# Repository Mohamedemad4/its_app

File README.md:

# its_app

### Schematics and PCB notes
 - 
### Notes on the SIM868 Module
 - it *needs* it's 2A peak current recommend connecting power to a battery
 - APN doens't really matter what you call it (at least Etisalat egypt)

### Notes about data_server
 - there is a 30char **hard** limit on token names
 - Expected Hz is .5Hz 
    - i.e 30 logs is a minute of data
 - #### About tokens 
    - We have 2 kinds of tokens
        - Client Tokens
            - Set by "login" on the client 
            - Used for Push notifications and everything else client related by car_token agnostic

        - Car Tokens
            - Preset in QR code on the Device it self
            - Multiple Client tokens can be registered to the Same Car Token
    - *ALL* Tokens are expected to look like 
        ```xxxx-xxx-xxxx``
        this is very critical for Car Tokens since the client expects this to be the case before sending them to the Server 
### Config Vars

#### data_server/tests/test_api.py
- email is the email to register the token with
- ```CAR_DATA_KEYS``` is the JSON keys expected as the output of the API for for the getData
- ```TOKEN_METADATA_KEYS``` is the JSON keys expected outputs of the API for get_metadata
- ```NOTF_KEYS``` is the JSON keys expected output of the API for get_notfs
- ```real_hz``` how often (in hertz) do we send the data to the server?
- ```min_of_speeding_to_alert``` how many minutes should pass before warning the user to a speed_exceeding event?
    - see #17
```
    server_uri="http://localhost:7060"
    email="mohamed.emad4bubble@gmail.com"
    CAR_DATA_KEYS=["car_token","lat","lot","speed","accuracy","Unixtimestamp"]
    TOKEN_METADATA_KEYS=["car_token","client_token","max_spd"]
    NOTF_KEYS=["client_token","title","msg"]
    real_hz=.5
```
#### data_server/notf_man.py
How many logs should pass before sending a warning notf?
```
    self.MAX_THROT_ENTRIES=15 # 30 logs means a min of speeding
```

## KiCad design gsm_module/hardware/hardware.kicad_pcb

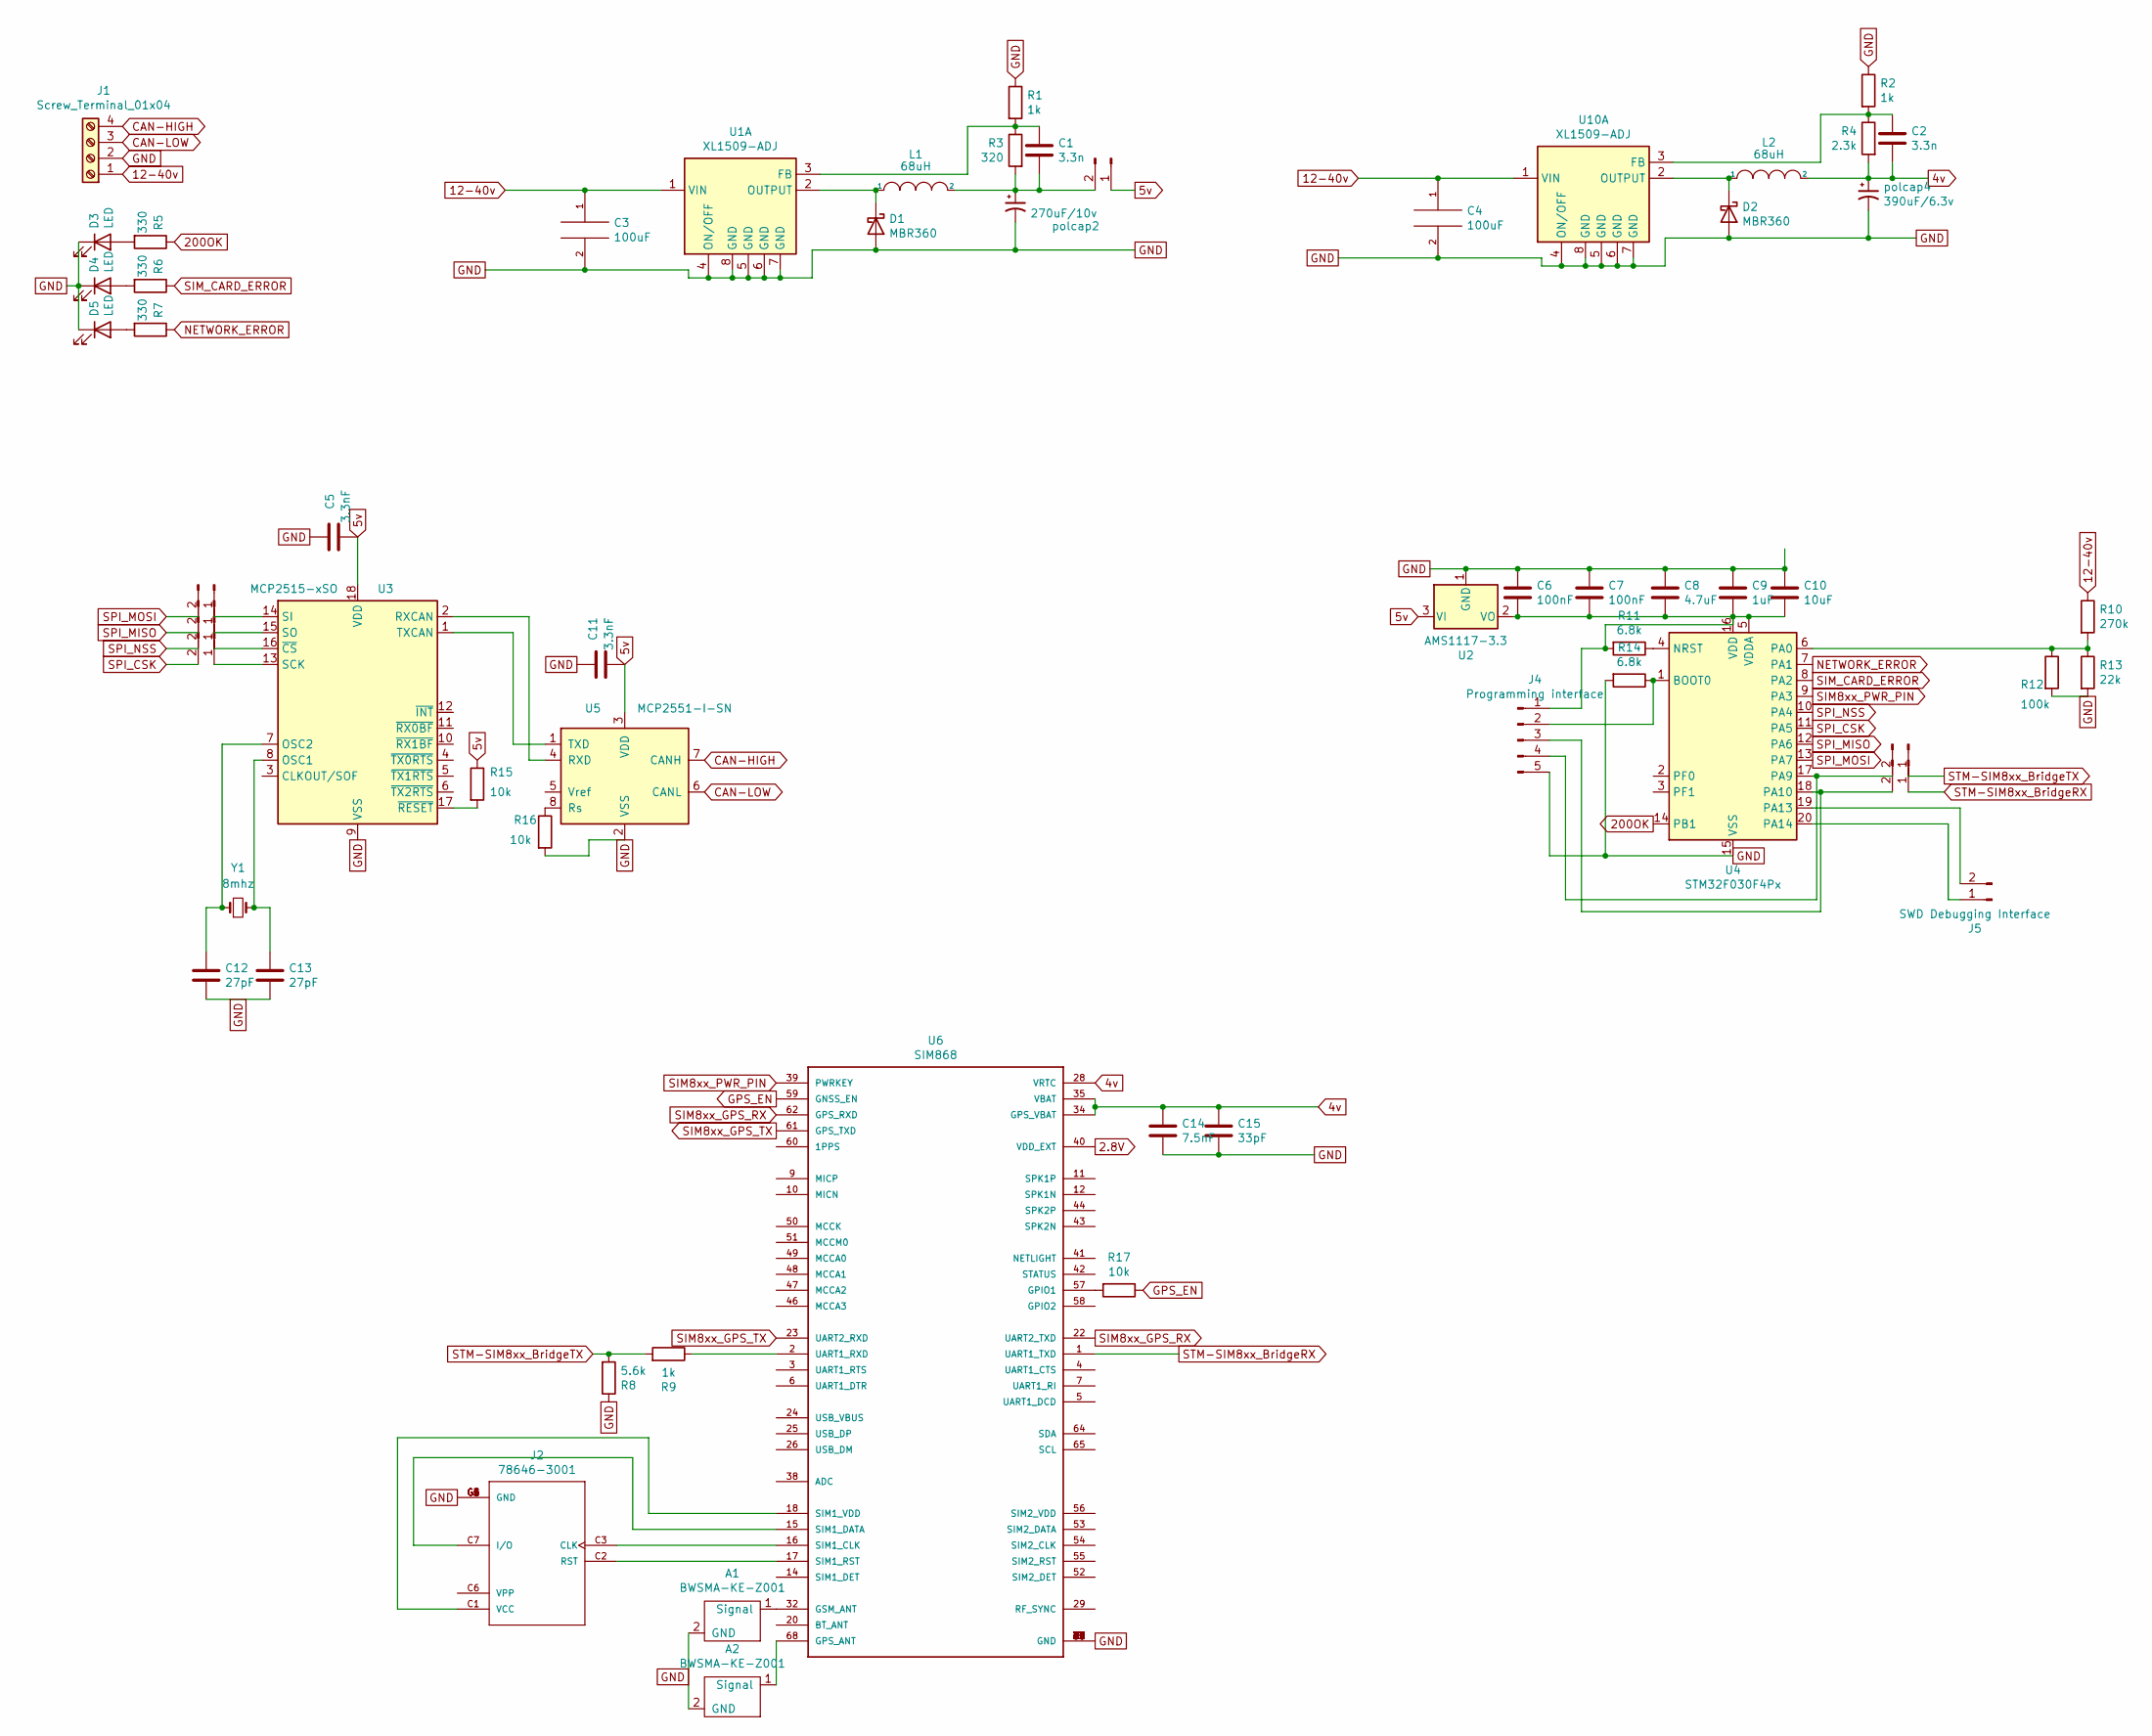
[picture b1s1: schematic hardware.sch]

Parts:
A1, A2: BWSMA-KE-Z001
C1, C2: 3.3n; C_Disc_D4.3mm_W1.9mm_P5.00mm
C3, C4: 100uF; CP_Radial_D8.0mm_P3.50mm
C5, C11: 3.3nF; C_Disc_D4.3mm_W1.9mm_P5.00mm
C6, C7: 100nF; C_Disc_D4.3mm_W1.9mm_P5.00mm
C8: 4.7uF; C_Disc_D4.3mm_W1.9mm_P5.00mm
C9: 1uF; C_Disc_D4.3mm_W1.9mm_P5.00mm
C10: 10uF; C_Disc_D4.3mm_W1.9mm_P5.00mm
C12, C13: 27pF; C_Disc_D4.3mm_W1.9mm_P5.00mm
C14: 7.5nF; C_Disc_D4.3mm_W1.9mm_P5.00mm
C15: 33pF; C_Disc_D4.3mm_W1.9mm_P5.00mm
D1, D2: MBR360; D_DO-201AD_P15.24mm_Horizontal
D3, D4, D5: LED; LED_D5.0mm
J1: Screw_Terminal_01x04; 5mm Pitch Screw Terminal 1x04
J2: 78646-3001; MOLEX_78646-3001
J4: Programming interface; PinHeader_1x05_P2.54mm_Vertical
J5: SWD Debugging Interface; PinHeader_1x02_P2.54mm_Vertical
J6, J8, J9, J10, J11, J12, J13: Conn_01x02_Male; PinHeader_1x02_P2.54mm_Vertical
L1, L2: 68uH; R_Axial_DIN0207_L6.3mm_D2.5mm_P10.16mm_Horizontal
R1, R2, R9: 1k; R_Axial_DIN0309_L9.0mm_D3.2mm_P12.70mm_Horizontal
R3: 320; R_Axial_DIN0309_L9.0mm_D3.2mm_P12.70mm_Horizontal
R4: 2.3k; R_Axial_DIN0309_L9.0mm_D3.2mm_P12.70mm_Horizontal
R5, R6, R7: 330; R_Axial_DIN0309_L9.0mm_D3.2mm_P12.70mm_Horizontal
R8: 5.6k; R_Axial_DIN0309_L9.0mm_D3.2mm_P12.70mm_Horizontal
R10: 270k; R_Axial_DIN0309_L9.0mm_D3.2mm_P12.70mm_Horizontal
R11, R14: 6.8k; R_Axial_DIN0309_L9.0mm_D3.2mm_P12.70mm_Horizontal
R12: 100k; R_Axial_DIN0309_L9.0mm_D3.2mm_P12.70mm_Horizontal
R13: 22k; R_Axial_DIN0309_L9.0mm_D3.2mm_P12.70mm_Horizontal
R15, R16, R17: 10k; R_Axial_DIN0309_L9.0mm_D3.2mm_P12.70mm_Horizontal
U1, U10: XL1509-ADJ; SOIC-8-1EP_3.9x4.9mm_P1.27mm_EP2.29x3mm
U2: AMS1117-3.3; SOT-223-3_TabPin2
U3: MCP2515-xSO; SOIC-18W_7.5x11.6mm_P1.27mm
U4: STM32F030F4Px; TSSOP-20_4.4x6.5mm_P0.65mm
U5: MCP2551-I-SN; SOIC-8_3.9x4.9mm_P1.27mm
U6: SIM868; XCVR_SIM868
Y1: 8mhz; Crystal_HC18-U_Vertical
polcap2: 270uF/10v; CP_Radial_D8.0mm_P3.50mm
polcap4: 390uF/6.3v; CP_Radial_D8.0mm_P3.50mm

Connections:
2.8V: U6.40 (VDD_EXT)
4v: C2.2, C14.1, C15.1, L2.2, R4.2, U6.28 (VRTC), U6.34 (GPS_VBAT), U6.35 (VBAT), polcap4.1
5v: C5.1, C11.1, J6.1, R15.1, U2.3 (VI), U3.18 (VDD), U5.3 (VDD)
12-40v: C3.1, C4.1, J1.1, R10.1, U1.1 (VIN), U10.1 (VIN)
200OK: R5.1, U4.14 (PB1)
CAN-HIGH: J1.4, U5.7 (CANH)
CAN-LOW: J1.3, U5.6 (CANL)
GND: A1.2 (GND), A2.2 (GND), C3.2, C4.2, C5.2, C6.1, C7.1, C8.1, C9.1, C10.1, C11.2, C12.2, C13.2, C14.2, C15.2, D1.2 (A), D2.2 (A), D3.1 (K), D4.1 (K), D5.1 (K), J1.2, J2.C5 (GND), J2.G1 (GND), J2.G2 (GND), J2.G3 (GND), J2.G4 (GND), J2.G5 (GND), J2.G6 (GND), J4.5, R1.1, R2.1, R8.1, R12.2, R13.2, R14.2, R16.2, U1.4 (ON/OFF), U1.5 (GND), U1.6 (GND), U1.7 (GND), U1.8 (GND), U2.1 (GND), U3.9 (VSS), U4.15 (VSS), U5.2 (VSS), U6.8 (GND), U6.13 (GND), U6.19 (GND), U6.21 (GND), U6.27 (GND), U6.30 (GND), U6.31 (GND), U6.33 (GND), U6.36 (GND), U6.37 (GND), U6.45 (GND), U6.63 (GND), U6.66 (GND), U6.67 (GND), U6.69 (GND), U6.70 (GND), U6.71 (GND), U6.72 (GND), U6.73 (GND), U6.74 (GND), U6.75 (GND), U6.76 (GND), U6.77 (GND), U10.4 (ON/OFF), U10.5 (GND), U10.6 (GND), U10.7 (GND), U10.8 (GND), polcap2.2, polcap4.2
GPS_EN: R17.1, U6.59 (GNSS_EN)
NETWORK_ERROR: R7.1, U4.7 (PA1)
unnamed: A1.1 (Signal), U6.32 (GSM_ANT)
unnamed: A2.1 (Signal), U6.68 (GPS_ANT)
unnamed: C1.1, R1.2, R3.1, U1.3 (FB)
unnamed: C1.2, J6.2, L1.2, R3.2, polcap2.1
unnamed: C2.1, R2.2, R4.1, U10.3 (FB)
unnamed: C6.2, C7.2, C8.2, C9.2, C10.2, J4.1, R11.2, U2.2 (VO), U4.5 (VDDA), U4.16 (VDD)
unnamed: C12.1, U3.7 (OSC2), Y1.1
unnamed: C13.1, U3.8 (OSC1), Y1.2
unnamed: D1.1 (K), L1.1, U1.2 (OUTPUT)
unnamed: D2.1 (K), L2.1, U10.2 (OUTPUT)
unnamed: D3.2 (A), R5.2
unnamed: D4.2 (A), R6.2
unnamed: D5.2 (A), R7.2
unnamed: J2.C1 (VCC), U6.18 (SIM1_VDD)
unnamed: J2.C2 (RST), U6.17 (SIM1_RST)
unnamed: J2.C3 (CLK), U6.16 (SIM1_CLK)
unnamed: J2.C7 (I/O), U6.15 (SIM1_DATA)
unnamed: J4.2, R14.1, U4.1 (BOOT0)
unnamed: J5.1, U4.20 (PA14)
unnamed: J5.2, U4.19 (PA13)
unnamed: J8.1, U3.14 (SI)
unnamed: J9.1, U3.15 (SO)
unnamed: J10.1, U3.16 (~CS)
unnamed: J11.1, U3.13 (SCK)
unnamed: J4.4, J12.2, U4.17 (PA9)
unnamed: J4.3, J13.2, U4.18 (PA10)
unnamed: R9.1, U6.2 (UART1_RXD)
unnamed: R10.2, R12.1, R13.1, U4.6 (PA0)
unnamed: R11.1, U4.4 (NRST)
unnamed: R15.2, U3.17 (~RESET)
unnamed: R16.1, U5.8 (Rs)
unnamed: R17.2, U6.57 (GPIO1)
unnamed: U3.1 (TXCAN), U5.1 (TXD)
unnamed: U3.2 (RXCAN), U5.4 (RXD)
SIM8xx_GPS_RX: U6.22 (UART2_TXD), U6.62 (GPS_RXD)
SIM8xx_GPS_TX: U6.23 (UART2_RXD), U6.61 (GPS_TXD)
SIM8xx_PWR_PIN: U4.9 (PA3), U6.39 (PWRKEY)
SIM_CARD_ERROR: R6.1, U4.8 (PA2)
SPI_CSK: J11.2, U4.11 (PA5)
SPI_MISO: J9.2, U4.12 (PA6)
SPI_MOSI: J8.2, U4.13 (PA7)
SPI_NSS: J10.2, U4.10 (PA4)
STM-SIM8xx_BridgeRX: J13.1, U6.1 (UART1_TXD)
STM-SIM8xx_BridgeTX: J12.1, R8.2, R9.2

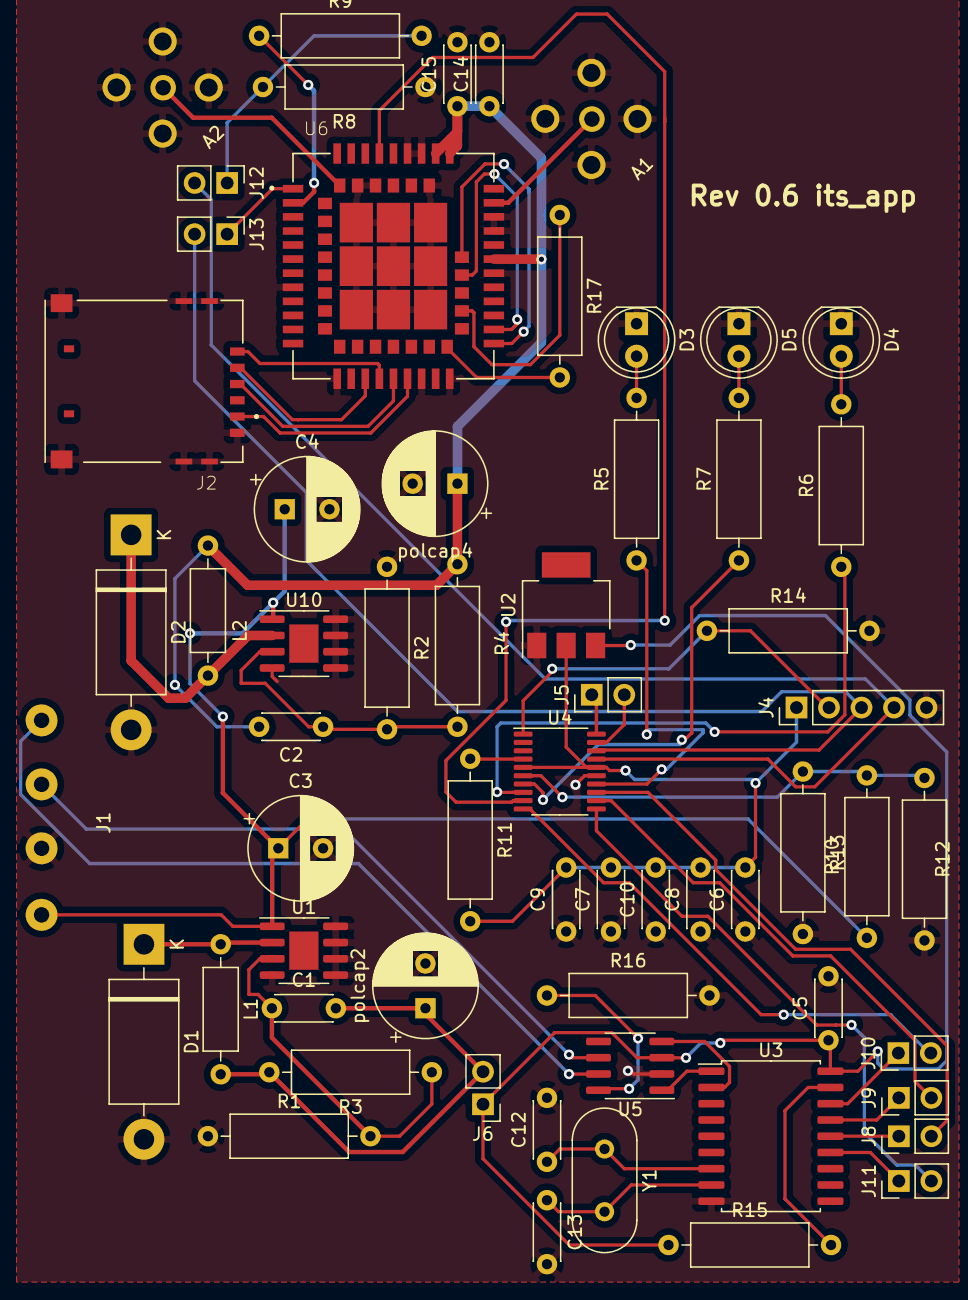
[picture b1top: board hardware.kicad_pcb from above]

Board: 2 copper layers, 61 parts (0 on the bottom side), 53 nets.

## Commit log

2020-07-07 base code just sends data on button press
2020-07-08 wrote Main API (UNTESTED)
2020-07-08 API tests ALL PASSED
2020-07-08 added Some Docs
2020-07-08 added Buildozer spec
2020-07-09 added base dashboard app map
2020-07-09 added better handling for tokens
2020-07-09 added new API endpoints for metadata
2020-07-10 base onboarding screen
2020-07-10 base skeleton with screenmanager and a help button
2020-07-10 added Help and no_connection screens,back mechanism ,and made all screens inheiret from the template_screen class
2020-07-10 fixed a back btn system bug and added unschduling to always check for internet event
2020-07-10 added map_screen
2020-07-10 added the 2 buttons to map_screen with correct size and pos
2020-07-10 removed KV files and added a better way to handle options and help btns
2020-07-10 show speed indicator
2020-07-11 options email change button story
2020-07-11 better way to handle option Screens and add new unit story
2020-07-11 change alert speed story
2020-07-11 added view other cars story (currently only 5 cars)
2020-07-11 added scrollView to view other cars no more limits! and finished all option stories
2020-07-11 made every page return JSON;add token registeration;add ping page
2020-07-11 Working API for v1 (UNTESTED)
2020-07-12 working onboarding and map_screen stories
2020-07-12 tested all User stories
2020-07-12 some docs in api file
2020-07-12 Working HTTP GET with GSM
2020-07-15 main GSM module code (UNTESTED)
2020-07-16 now works for Nano and parses URI correctly
2020-07-16 gsm Module prototype now working!
2020-07-17 some notes and housekeeping
2020-07-17 disregared reading if it's later than 2m;made it so data can be logged if the token isn't registered but is valid
2020-07-17 state handeling if user opens the app on no_conn screen;a more robust get_all_vars()
2020-07-17 fixed #1 by adding an on_leave method to onboarding
2020-07-22 garbage code for GSM location test
2020-07-26 ready for GSMLoc/GPS expirement
2020-08-03 SIM800C bare schematic with MCU and power
2020-08-03 all but the CANSTACK
2020-08-04 SIM800 Breakout+CANSTACK Rev1 schematic
2020-08-05 Rev 1 schematic all footprints done
2020-08-06 rev 1.5 final
2020-08-08 rev 1.6 (changed SMT antenna)
2020-08-09 rev .5 PCB motherfucker (we-ho)
2020-08-21 PCB rev 0.8
2020-08-21 added Push notfs for android
2020-08-21 something idk.
2020-08-21 deleted old python clients
2020-08-22 added base react client
2020-08-22 Added AsyncStorage
2020-08-24 Fixed #21
2020-08-24 Signup Mockup with QR code reader
2020-08-25 onboarding Flow
2020-08-25 View other cars screen
2020-08-25 newest PCB no acid traps all up to spec
2020-08-26 fixed #2
2020-08-27 base OSM map screen (but it crashes)
2020-08-27 added leaflet dep
2020-09-29 renamed Map from TSX to js add android config
